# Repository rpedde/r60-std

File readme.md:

# r60 std #

This is just a simple poker 60% board as a base for testing
stuff.

It's a 16MHz Atmega32U4 running [quantum mechanical
keyboard](https://github.com/qmk/qmk_firmware) firmware.

It should fit in most (all?) 60% poker cases.

## CAD/CAM ##

I have cnc milled plates for this board using openscad/dxf files generated
from [this project](https://github.com/rpedde/platemaker).

I have cnc milled cases for this board using openscad/stl files generate
from [this project](https://github.com/rpedde/r60-case).

## Changelog ##

Rev 1 (Ordered through easyeda, verified working):

 - Initial rev

Rev 1.1 (Ordered through easyeda, verified working) [gerbers](https://storage.googleapis.com/rpedde-public-gerbers/r60-std-r1.1.zip):

 - Changed PTH holes on sides to edge slot cuts, for ease in mfg

Rev 1.2 (Not verified working):

 - Silkscreen fixes
 - Move speaker connector, allow for direct drive of 8 ohm speaker

Rev 2.0 (Not verified working) [gerbers](https://storage.googleapis.com/rpedde-public-gerbers/r60-std-r2.0.zip):

 - Use SMT diodes rather than through-hole
 - Align components to fit better on vortex cases (braces between rows)

Rev 2.1 (Not verified working) [gerbers](https://storage.googleapis.com/rpedde-public-gerbers/r60-std-r2.1.zip)

 - Switch SOD-323 footprint diodes to 0805

Rev 3.0 (ISO working, fitment problems with ANSI) [gerbers](https://storage.googleapis.com/rpedde-public-gerbers/r60-std-r3.0.zip):

 - Add option for stepped capslock/control
 - Add option for ISO as well as ANSI

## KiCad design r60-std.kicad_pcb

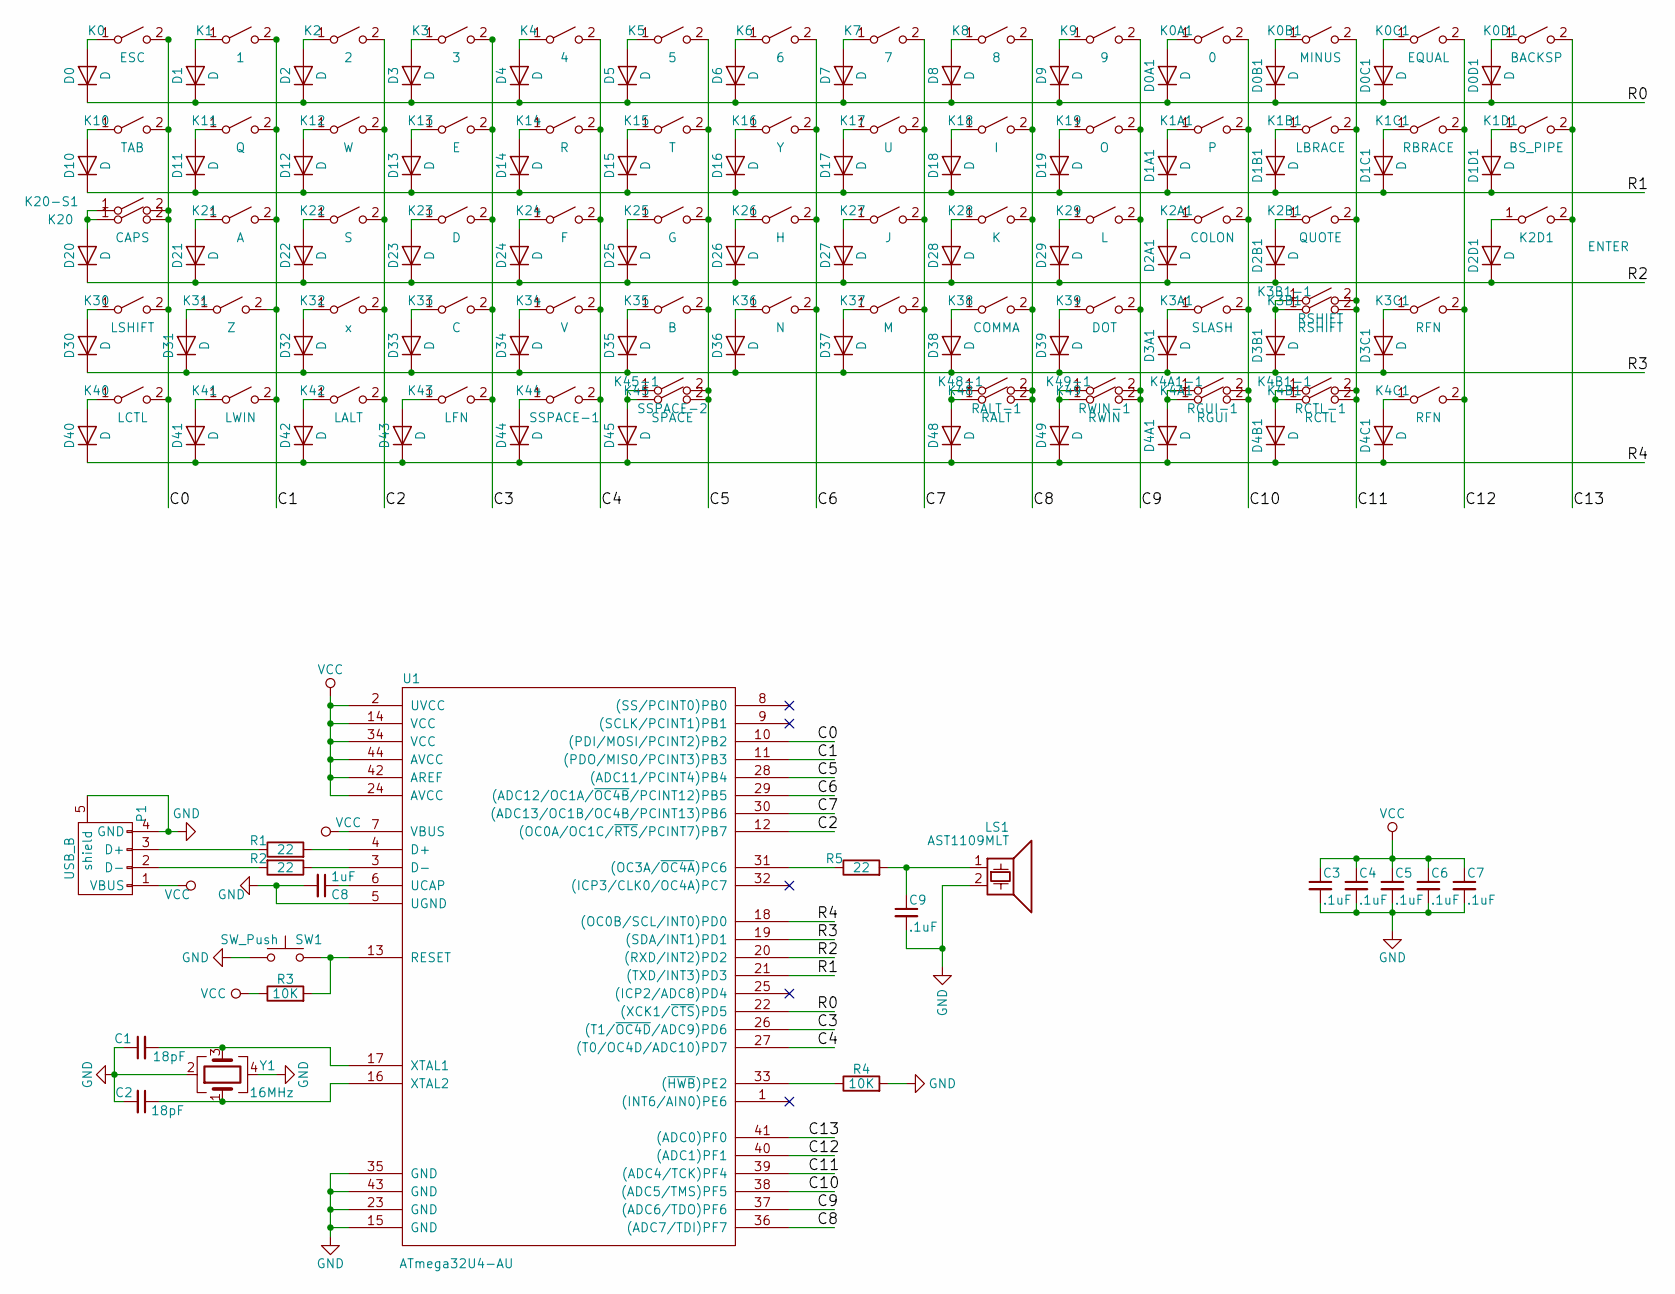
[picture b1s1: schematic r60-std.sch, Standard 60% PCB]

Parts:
C1, C2: 18pF; C_0603
C3, C4, C5, C6, C7: .1uF; C_0603
C8: 1uF; C_0603
C9: .1uF; C_0805
D0, D0A1, D0B1, D0C1, D0D1, D1, D1A1, D1B1, D1C1, D1D1, D2, D2A1, D2B1, D2D1, D3, D3A1, D3B1, D3C1, D4, D4A1, D4B1, D4C1, D5, D6, D7, D8, D9, D10, D11, D12, D13, D14, D15, D16, D17, D18, D19, D20, D21, D22, D23, D24, D25, D26, D27, D28, D29, D30, D31, D32, D33, D34, D35, D36, D37, D38, D39, D40, D41, D42, D43, D44, D45, D48, D49: D; D_0805
K0: ESC; CHERRY_PCB_100H
K0A1: 0; CHERRY_PCB_100H
K0B1: MINUS; CHERRY_PCB_100H
K0C1: EQUAL; CHERRY_PCB_100H
K0D1: BACKSP; CHERRY_PCB_200H_INVERTED
K1: 1; CHERRY_PCB_100H
K1A1: P; CHERRY_PCB_100H
K1B1: LBRACE; CHERRY_PCB_100H
K1C1: RBRACE; CHERRY_PCB_100H
K1D1: BS_PIPE; CHERRY_PCB_150H
K2: 2; CHERRY_PCB_100H
K2A1: COLON; CHERRY_PCB_100H
K2B1: QUOTE; CHERRY_PCB_100H
K2D1: ENTER; CHERRY_PCB_225H
K3: 3; CHERRY_PCB_100H
K3A1: SLASH; CHERRY_PCB_100H
K3B1: RSHIFT; CHERRY_PCB_275H
K3B1-1: RSHIFT; CHERRY_PCB_175H
K3C1, K4C1: RFN; CHERRY_PCB_100H
K4: 4; CHERRY_PCB_100H
K4A1: RGUI; CHERRY_PCB_125H
K4A1-1: RGUI-1; CHERRY_PCB_100H
K4B1: RCTL; CHERRY_PCB_125H
K4B1-1: RCTL-1; CHERRY_PCB_100H
K5: 5; CHERRY_PCB_100H
K6: 6; CHERRY_PCB_100H
K7: 7; CHERRY_PCB_100H
K8: 8; CHERRY_PCB_100H
K9: 9; CHERRY_PCB_100H
K10: TAB; CHERRY_PCB_150H
K11: Q; CHERRY_PCB_100H
K12: W; CHERRY_PCB_100H
K13: E; CHERRY_PCB_100H
K14: R; CHERRY_PCB_100H
K15: T; CHERRY_PCB_100H
K16: Y; CHERRY_PCB_100H
K17: U; CHERRY_PCB_100H
K18: I; CHERRY_PCB_100H
K19: O; CHERRY_PCB_100H
K20: CAPS; CHERRY_PCB_175H
K20-S1: CAPS; CHERRY_PCB_125H
K21: A; CHERRY_PCB_100H
K22: S; CHERRY_PCB_100H
K23: D; CHERRY_PCB_100H
K24: F; CHERRY_PCB_100H
K25: G; CHERRY_PCB_100H
K26: H; CHERRY_PCB_100H
K27: J; CHERRY_PCB_100H
K28: K; CHERRY_PCB_100H
K29: L; CHERRY_PCB_100H
K30: LSHIFT; CHERRY_PCB_225H
K31: Z; CHERRY_PCB_100H
K32: x; CHERRY_PCB_100H
K33: C; CHERRY_PCB_100H
K34: V; CHERRY_PCB_100H
K35: B; CHERRY_PCB_100H
K36: N; CHERRY_PCB_100H
K37: M; CHERRY_PCB_100H
K38: COMMA; CHERRY_PCB_100H
K39: DOT; CHERRY_PCB_100H
K40: LCTL; CHERRY_PCB_125H
K41: LWIN; CHERRY_PCB_125H
K42: LALT; CHERRY_PCB_125H
K43: LFN; CHERRY_PCB_125H
K44: SSPACE-1; CHERRY_PCB_225H
K45: SPACE; CHERRY_PCB_625H
K45-1: SSPACE-2; CHERRY_PCB_275H
K48: RALT; CHERRY_PCB_125H
K48-1: RALT-1; CHERRY_PCB_100H
K49: RWIN; CHERRY_PCB_125H
K49-1: RWIN-1; CHERRY_PCB_100H
LS1: AST1109MLT; AST1109ML-SMT
P1: USB_B; USB_Mini-B
R1, R2, R5: 22; RC_0805
R3: 10K; RC_0805
R4: 10K; R_0603
SW1: SW_Push; SW_SPST_TL3342
U1: ATmega32U4-AU; QFN-44-1EP_7x7mm_Pitch0.5mm
Y1: 16MHz; Crystal_SMD_3225-4pin_3.2x2.5mm

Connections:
/C0: K0.2 (B), K10.2 (B), K20.2 (B), K20-S1.2 (B), K30.2 (B), K40.2 (B), U1.10 ((PDI/MOSI/PCINT2)PB2)
/C1: K1.2 (B), K11.2 (B), K21.2 (B), K31.2 (B), K41.2 (B), U1.11 ((PDO/MISO/PCINT3)PB3)
/C2: K2.2 (B), K12.2 (B), K22.2 (B), K32.2 (B), K42.2 (B), U1.12 ((OC0A/OC1C/~RTS~/PCINT7)PB7)
/C3: K3.2 (B), K13.2 (B), K23.2 (B), K33.2 (B), K43.2 (B), U1.26 ((T1/~OC4D~/ADC9)PD6)
/C4: K4.2 (B), K14.2 (B), K24.2 (B), K34.2 (B), K44.2 (B), U1.27 ((T0/OC4D/ADC10)PD7)
/C5: K5.2 (B), K15.2 (B), K25.2 (B), K35.2 (B), K45.2 (B), K45-1.2 (B), U1.28 ((ADC11/PCINT4)PB4)
/C6: K6.2 (B), K16.2 (B), K26.2 (B), K36.2 (B), U1.29 ((ADC12/OC1A/~OC4B~/PCINT12)PB5)
/C7: K7.2 (B), K17.2 (B), K27.2 (B), K37.2 (B), U1.30 ((ADC13/OC1B/OC4B/PCINT13)PB6)
/C8: K8.2 (B), K18.2 (B), K28.2 (B), K38.2 (B), K48.2 (B), K48-1.2 (B), U1.36 ((ADC7/TDI)PF7)
/C9: K9.2 (B), K19.2 (B), K29.2 (B), K39.2 (B), K49.2 (B), K49-1.2 (B), U1.37 ((ADC6/TDO)PF6)
/C10: K0A1.2 (B), K1A1.2 (B), K2A1.2 (B), K3A1.2 (B), K4A1.2 (B), K4A1-1.2 (B), U1.38 ((ADC5/TMS)PF5)
/C11: K0B1.2 (B), K1B1.2 (B), K2B1.2 (B), K3B1.2 (B), K3B1-1.2 (B), K4B1.2 (B), K4B1-1.2 (B), U1.39 ((ADC4/TCK)PF4)
/C12: K0C1.2 (B), K1C1.2 (B), K3C1.2 (B), K4C1.2 (B), U1.40 ((ADC1)PF1)
/C13: K0D1.2 (B), K1D1.2 (B), K2D1.2 (B), U1.41 ((ADC0)PF0)
/R0: D0.1 (K), D0A1.1 (K), D0B1.1 (K), D0C1.1 (K), D0D1.1 (K), D1.1 (K), D2.1 (K), D3.1 (K), D4.1 (K), D5.1 (K), D6.1 (K), D7.1 (K), D8.1 (K), D9.1 (K), U1.22 ((XCK1/~CTS~)PD5)
/R1: D1A1.1 (K), D1B1.1 (K), D1C1.1 (K), D1D1.1 (K), D10.1 (K), D11.1 (K), D12.1 (K), D13.1 (K), D14.1 (K), D15.1 (K), D16.1 (K), D17.1 (K), D18.1 (K), D19.1 (K), U1.21 ((TXD/INT3)PD3)
/R2: D2A1.1 (K), D2B1.1 (K), D2D1.1 (K), D20.1 (K), D21.1 (K), D22.1 (K), D23.1 (K), D24.1 (K), D25.1 (K), D26.1 (K), D27.1 (K), D28.1 (K), D29.1 (K), U1.20 ((RXD/INT2)PD2)
/R3: D3A1.1 (K), D3B1.1 (K), D3C1.1 (K), D30.1 (K), D31.1 (K), D32.1 (K), D33.1 (K), D34.1 (K), D35.1 (K), D36.1 (K), D37.1 (K), D38.1 (K), D39.1 (K), U1.19 ((SDA/INT1)PD1)
/R4: D4A1.1 (K), D4B1.1 (K), D4C1.1 (K), D40.1 (K), D41.1 (K), D42.1 (K), D43.1 (K), D44.1 (K), D45.1 (K), D48.1 (K), D49.1 (K), U1.18 ((OC0B/SCL/INT0)PD0)
GND: C1.1, C2.2, C3.2, C4.2, C5.2, C6.2, C7.2, C8.2, C9.2, LS1.2, P1.4 (GND), P1.5 (shield), R4.2, SW1.1, U1.5 (UGND), U1.15 (GND), U1.23 (GND), U1.35 (GND), U1.43 (GND), U1.45, Y1.2, Y1.4
unnamed: C1.2, U1.17 (XTAL1), Y1.3
unnamed: C2.1, U1.16 (XTAL2), Y1.1
unnamed: C8.1, U1.6 (UCAP)
unnamed: C9.1, LS1.1, R5.2
unnamed: D0.2 (A), K0.1 (A)
unnamed: D0A1.2 (A), K0A1.1 (A)
unnamed: D0B1.2 (A), K0B1.1 (A)
unnamed: D0C1.2 (A), K0C1.1 (A)
unnamed: D0D1.2 (A), K0D1.1 (A)
unnamed: D1.2 (A), K1.1 (A)
unnamed: D1A1.2 (A), K1A1.1 (A)
unnamed: D1B1.2 (A), K1B1.1 (A)
unnamed: D1C1.2 (A), K1C1.1 (A)
unnamed: D1D1.2 (A), K1D1.1 (A)
unnamed: D2.2 (A), K2.1 (A)
unnamed: D2A1.2 (A), K2A1.1 (A)
unnamed: D2B1.2 (A), K2B1.1 (A)
unnamed: D2D1.2 (A), K2D1.1 (A)
unnamed: D3.2 (A), K3.1 (A)
unnamed: D3A1.2 (A), K3A1.1 (A)
unnamed: D3B1.2 (A), K3B1.1 (A), K3B1-1.1 (A)
unnamed: D3C1.2 (A), K3C1.1 (A)
unnamed: D4.2 (A), K4.1 (A)
unnamed: D4A1.2 (A), K4A1.1 (A), K4A1-1.1 (A)
unnamed: D4B1.2 (A), K4B1.1 (A), K4B1-1.1 (A)
unnamed: D4C1.2 (A), K4C1.1 (A)
unnamed: D5.2 (A), K5.1 (A)
unnamed: D6.2 (A), K6.1 (A)
unnamed: D7.2 (A), K7.1 (A)
unnamed: D8.2 (A), K8.1 (A)
unnamed: D9.2 (A), K9.1 (A)
unnamed: D10.2 (A), K10.1 (A)
unnamed: D11.2 (A), K11.1 (A)
unnamed: D12.2 (A), K12.1 (A)
unnamed: D13.2 (A), K13.1 (A)
unnamed: D14.2 (A), K14.1 (A)
unnamed: D15.2 (A), K15.1 (A)
unnamed: D16.2 (A), K16.1 (A)
unnamed: D17.2 (A), K17.1 (A)
unnamed: D18.2 (A), K18.1 (A)
unnamed: D19.2 (A), K19.1 (A)
unnamed: D20.2 (A), K20.1 (A), K20-S1.1 (A)
unnamed: D21.2 (A), K21.1 (A)
unnamed: D22.2 (A), K22.1 (A)
unnamed: D23.2 (A), K23.1 (A)
unnamed: D24.2 (A), K24.1 (A)
unnamed: D25.2 (A), K25.1 (A)
unnamed: D26.2 (A), K26.1 (A)
unnamed: D27.2 (A), K27.1 (A)
unnamed: D28.2 (A), K28.1 (A)
unnamed: D29.2 (A), K29.1 (A)
unnamed: D30.2 (A), K30.1 (A)
unnamed: D31.2 (A), K31.1 (A)
unnamed: D32.2 (A), K32.1 (A)
unnamed: D33.2 (A), K33.1 (A)
unnamed: D34.2 (A), K34.1 (A)
unnamed: D35.2 (A), K35.1 (A)
unnamed: D36.2 (A), K36.1 (A)
unnamed: D37.2 (A), K37.1 (A)
unnamed: D38.2 (A), K38.1 (A)
unnamed: D39.2 (A), K39.1 (A)
unnamed: D40.2 (A), K40.1 (A)
unnamed: D41.2 (A), K41.1 (A)
unnamed: D42.2 (A), K42.1 (A)
unnamed: D43.2 (A), K43.1 (A)
unnamed: D44.2 (A), K44.1 (A)
unnamed: D45.2 (A), K45.1 (A), K45-1.1 (A)
unnamed: D48.2 (A), K48.1 (A), K48-1.1 (A)
unnamed: D49.2 (A), K49.1 (A), K49-1.1 (A)
unnamed: P1.2 (D-), R2.2
unnamed: P1.3 (D+), R1.1
unnamed: R1.2, U1.4 (D+)
unnamed: R2.1, U1.3 (D-)
unnamed: R3.2, SW1.2, U1.13 (RESET)
unnamed: R4.1, U1.33 ((~HWB~)PE2)
unnamed: R5.1, U1.31 ((OC3A/~OC4A~)PC6)
VCC: C3.1, C4.1, C5.1, C6.1, C7.1, P1.1 (VBUS), R3.1, U1.2 (UVCC), U1.7 (VBUS), U1.14 (VCC), U1.24 (AVCC), U1.34 (VCC), U1.42 (AREF), U1.44 (AVCC)

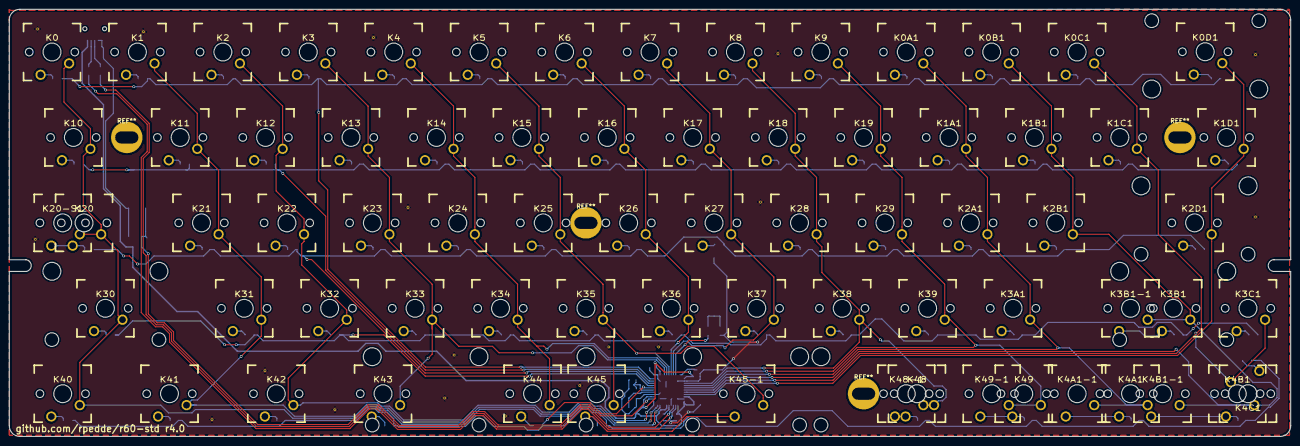
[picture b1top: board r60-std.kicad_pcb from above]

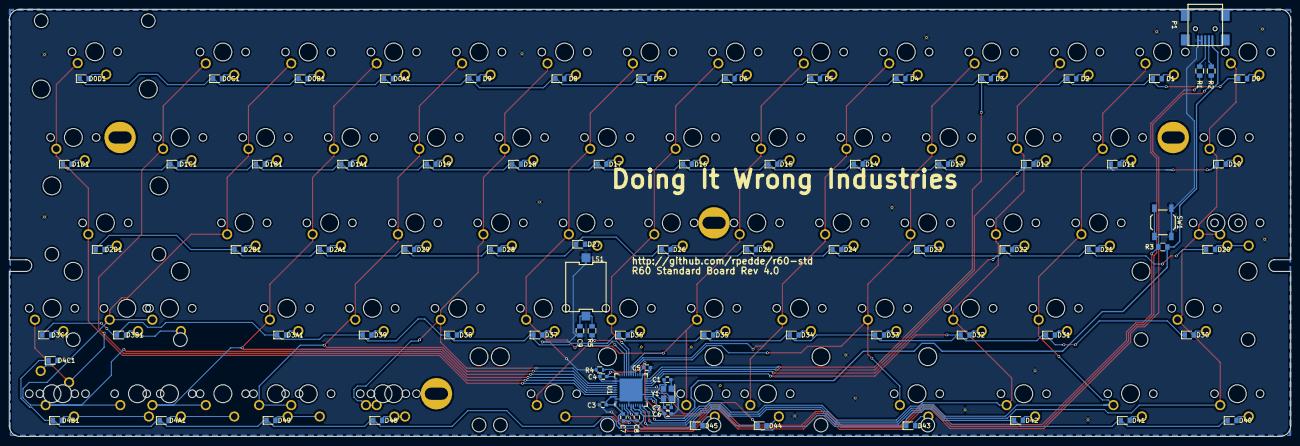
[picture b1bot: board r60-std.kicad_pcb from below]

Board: 2 copper layers, 285.8 x 95.3 mm, 156 parts (84 on the bottom side), 97 nets.

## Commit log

2017-08-19 Initial version
2017-08-19 Change cut edge holes to slot cuts
2017-08-19 add readme
2017-08-23 Fix silkscreen, move speaker connector, add speaker hardware
2017-08-31 add qmk firmware
2017-10-04 start on r2.0 board
2017-10-05 missing some ground pads
2017-10-07 generate r2.0 gerbers
2018-01-06 switch to 0805 diodes
2018-01-24 Expand out 0805 pads on both r and d
    re-route some traces as a consequence.
2018-03-26 add ISO and stepped capslock support
2018-04-04 update firmware
2018-04-04 firmware readme fixes
2018-04-04 firmware readme fixes for real
2018-04-09 update firmware for rev3 boards
2018-05-07 missing a firmware file
2018-05-07 First pass at r4 design
    Remove ISO layouts, keep stepped capslock/ctrl. Allow for
    either 6.25u space or 1.25/2.25/2.75 split space. Move to
    0603 footprints near atmega to handle smaller space due to
    split spacebar. Switch atmega from -AU in 44 TQFP to -MU
    part in 44 QFN, again to deal with less room due to split
    spacebar.
2018-05-07 inform of working config
2018-05-10 add option for split right shift
2018-05-21 default 60% firmware for rev4 boards
